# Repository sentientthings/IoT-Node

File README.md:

# IoT-Node
Hardware design files for the Sentient Things Iot Node

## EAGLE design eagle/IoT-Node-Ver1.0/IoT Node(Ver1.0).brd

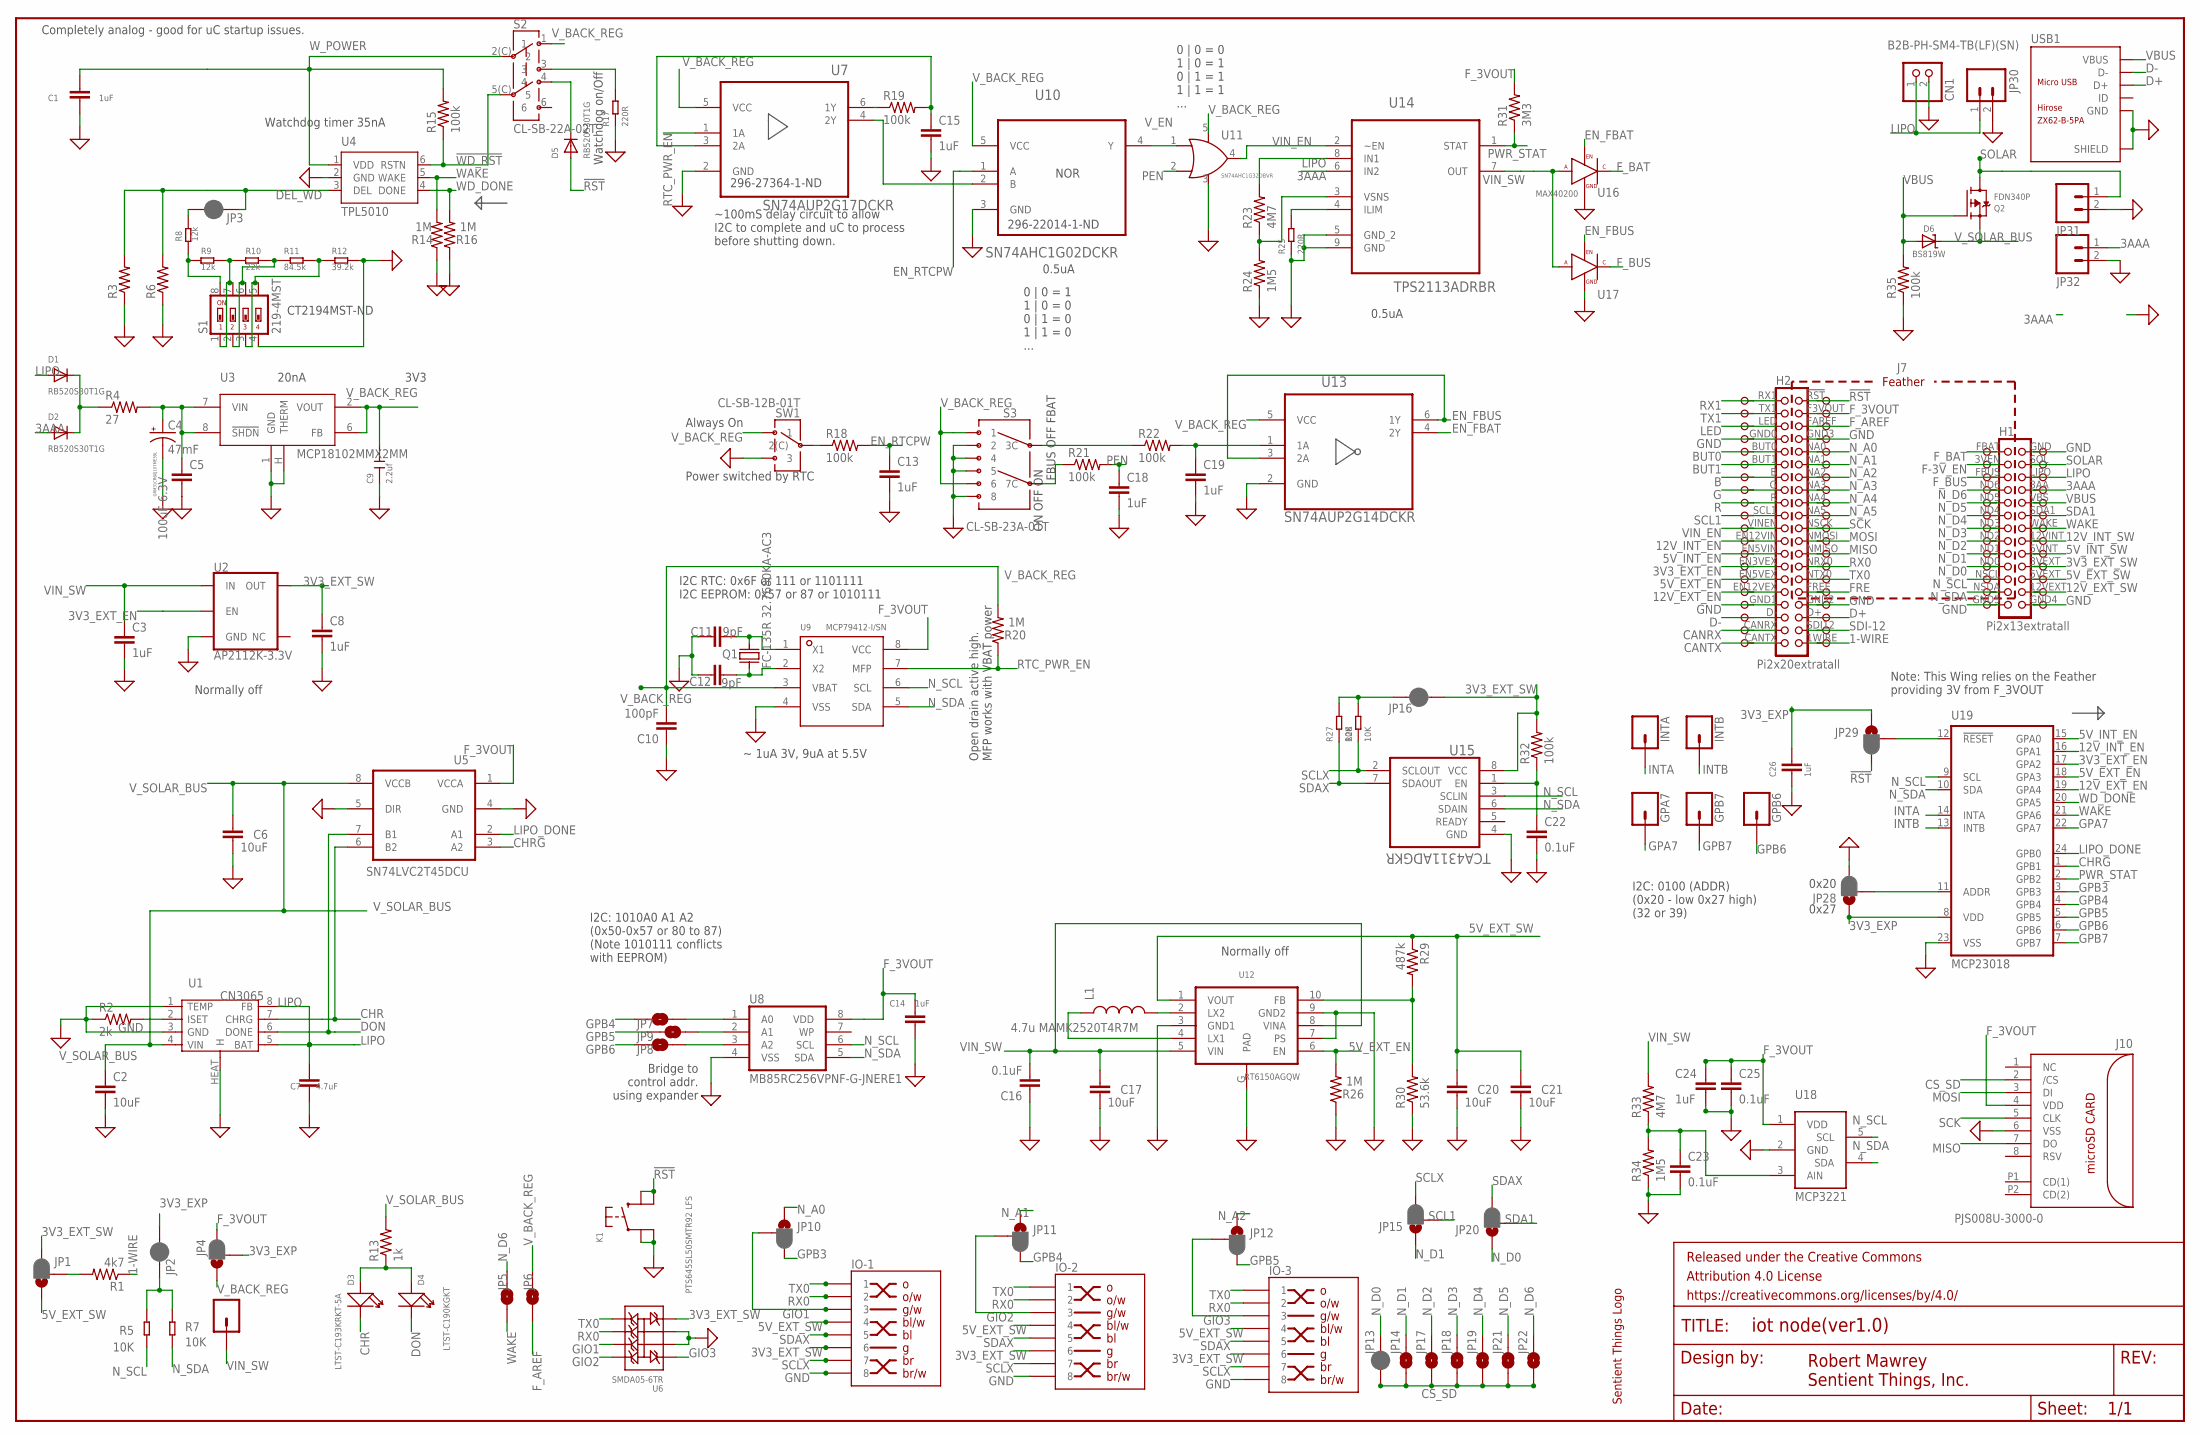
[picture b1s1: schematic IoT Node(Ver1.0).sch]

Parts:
C1, C3, C8, C13, C14, C15, C18, C19, C24, C26: 1uF; 0603-CAP; PARTNO CL10A105KP8NNNC
C2, C6, C17, C20, C21: 10uF; 0805; PARTNO CL21A106KPFNNNE
C4: 47mF; CAP-10.5MM; PARTNO FC0H473ZFTBR24
C5: 100uF 6.3V; C1206; PARTNO DNP
C7: 4.7uF; 0805; PARTNO CL10A475KP8NNNC
C9: 2.2uf; C0603; PARTNO CL10A106MQ8NNNC
C10: 100pF; 0805; PARTNO CL21C101JC61PNC
C11, C12: 9pF; 0603; PARTNO C1608C0G1H090D080AA
C16, C22, C23, C25: 0.1uF; 0603-CAP; PARTNO CL10F104ZB8NNNC
CN1: B2B-PH-SM4-TB(LF)(SN); JST-PH-2-SMT; PARTNO B2B-PH-SM4-TB(LF)(SN)?
D1, D2, D5: RB520S30T1G; SOD-523; PARTNO RB520S30T1G
D3: LTST-C193KRKT-5A; D0603; PARTNO LTST-C193KRKT-5A
D4: LTST-C190KGKT; D0603; PARTNO LTST-C190KGKT
D6: BS819W; SOD-123; PARTNO B5819WS-TP
FRAME1: FRAME-LEDGER; CREATIVE_COMMONS
GPA7: M01SMD-4.5X1.5; PAD-1.5X4.5; PARTNO DNP
GPB6, GPB7: M01SMD-4.5X1.5; PAD-1.5X4.5; PARTNO DNP
H1: Pi2x13extratall; 2X13PLACEMENT; PARTNO 2X13-ExtraTall
H2: Pi2x20extratall; 2X20PLACEMENT; PARTNO 2X20ExtraTall
INTA: M01SMD-4.5X1.5; PAD-1.5X4.5; PARTNO DNP
INTB: M01SMD-4.5X1.5; PAD-1.5X4.5; PARTNO DNP
IO-1, IO-2, IO-3: RJ45-8NODE-HOR; 73304111LF; PARTNO 73304-111LF
J1: CONN_01; 1X01; PARTNO DNP
J5, J6: M20IOTNODE; M20NODE; PARTNO DNP
J7: IOTNODEDOUBLE; IOTNODE; PARTNO DNP
J8, J9: M13NODE; 1X13NODE; PARTNO DNP
J10: PJS008U-3000-0; MICROSDYAMAICHI; PARTNO PJS008U-3000-0
JP1, JP4, JP10, JP11, JP12, JP15, JP20, JP28, JP29: JUMPER-SMT_3_1-NC_PASTE_NO-SILK; SMT-JUMPER_3_1-NC_PASTE_NO-SILK; PARTNO DNP
JP2, JP3, JP13, JP16: JUMPER-SMT_2_NC_PASTE_NO-SILK; SMT-JUMPER_2_NC_PASTE_NO-SILK; PARTNO DNP
JP5, JP6, JP7, JP8, JP9, JP14, JP17, JP18, JP19, JP21, JP22: JUMPER-SMT_2_NO_NO-SILK; SMT-JUMPER_2_NO_NO-SILK; PARTNO DNP
JP30: M021X02_LOCK_FEM; 1X02_LOCK_FEM; PARTNO 691322110002
JP31: M02SOCK; 1X02-3.5-HOR; PARTNO DNP
JP32: M02PLUG; 1X02_3.5TERM; PARTNO 691321100002
K1: PTS645SL50SMTR92 LFS; TACTILE6MM-ESWITCH; PARTNO PTS645SL50SMTR92 LFS
L1: 4.7u MAMK2520T4R7M; 2520; PARTNO MAMK2520T2R2M
N1: SENTIENTLOGO-ULP; SENTIENT_THINGS+50MM_TPLACE_BMP; PARTNO DNP
Q1: FC-135R 32.7680KA-AC3; FC135; PARTNO FC-135R 32.7680KA-AC3
Q2: FDN340P; SOT23-R; PARTNO FDN340P
R1: 4k7; 0603-RES; PARTNO RC0603JR-074K7L
R2: 2k; R0603; PARTNO ERJ-3GEYJ202V
R3, R6: RESISTOR0603-RES; 0603-RES; PARTNO DNP
R4: 27; 0603-RES; PARTNO RC0603JR-0727RL
R5, R7, R27, R28: 10K; R0603; PARTNO ERJ-3GEYJ103V
R8, R9: 12k; R0603; PARTNO ERJ-3GEYJ123V
R10: 22k; R0603; PARTNO ERJ-3GEYJ223V
R11: 84.5k; 0603; PARTNO RC0603FR-0784K5L
R12: 39.2k; 0603; PARTNO RC0603FR-0739K2L
R13: 1k; R0603; PARTNO ERJ-3GEYJ102V
R14, R16, R20, R26: 1M; 0603; PARTNO ERJ-3GEYJ105V
R15, R18, R19, R21, R22, R32, R35: 100k; 0603-RES; PARTNO ERJ-3GEYJ104V
R17, R25: 220R; R0603; PARTNO ERJ-3GEYJ221V
R23, R33: 4M7; 0603-RES; PARTNO ERJ-3GEYJ475V
R24, R34: 1M5; 0603-RES; PARTNO ERJ-3GEYJ155V
R29: 487k; 0603-RES; PARTNO RC0603FR-07487KL
R30: 53.6k; 0603-RES; PARTNO RC0603FR-0753K6L
R31: 3M3; 0603-RES; PARTNO ERJ-3GEYJ335V
S1: 219-4MST; SMS-004; PARTNO 219-4MST
S2: CL-SB-22A-02T; CL-SB-22A; PARTNO CL-SB-22A-02T
S3: CL-SB-23A-01T; CL-SB-23A; PARTNO CL-SB-23A-01T
SW1: CL-SB-12B-01T; CL-SB-12B; PARTNO CL-SB-12B-01T
U1: CN3065; DFN8; PARTNO CN3065
U2: AP2112K-3.3V; SOT23-5; PARTNO AP2112K-3.3TRG
U3: MCP18102MMX2MM; 8VDFN; PARTNO MCP1810T-33I/J8A
U4: TPL5010; SOT23-6; PARTNO TPL5010DDCT
U5: SN74LVC2T45DCU; US8-DCU; PARTNO SN74LVC2T45DCUR
U6: SMDA05-6TR; SOIC-8-STANDARD; PARTNO SMDA05-6TR
U7: SN74AUP2G17DCKR; SOT65P210X110-6N
U8: MB85RC256VPNF-G-JNERE1; SO08; PARTNO MB85RC256VPNF-G-JNERE1
U9: MCP79412-I/SN; RTC_MCP7941X; PARTNO MCP79412-I/SN
U10: SN74AHC1G02DCKR; SOT65P210X110-5N
U11: SN74AHC1G32DBVR; SOT23-5; PARTNO SN74AHC1G32DBVR
U12: RT6150AGQW; DFN103X3; PARTNO RT6150AGQW
U13: SN74AUP2G14DCKR; SOT65P210X110-6N
U14: TPS2113ADRBR; SON65P300X300X100-9N
U15: TCA4311ADGKR; SOP65P490X110-8N; PARTNO TCA4311ADGKR
U16, U17: MAX40200; SOT23-5; PARTNO MAX40200AUK+T
U18: MCP3221; SOT23-5; PARTNO MCP3221A5T-E/OT
U19: MCP23018; QFN24-4MM; PARTNO MCP23018-E/MJ
USB1: ZX62-B-5PA; MICRO-USB5+6P-SMD-0.65-AB; PARTNO ZX62-B-5PA(33)

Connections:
1-WIRE: J6.20, J7.1WIRE (40), R1.1
3AAA: D2.A, J7.3AA (60), J9.4, JP32.1, U14.6 (IN2)
3V3_EXP: C26.1, JP2.1, JP4.2, JP28.1, JP29.1, U19.8 (VDD)
3V3_EXT_EN: J5.14, J7.EN3VEX (27), U2.3 (EN), U19.17 (GPA2)
3V3_EXT_SW: C8.1, IO-1.6, IO-2.6, IO-3.6, J7.3VEXT (48), J9.10, JP1.3, JP16.1, R32.2, U2.5 (OUT), U6.8, U15.8 (VCC)
5V_EXT_EN: J5.15, J7.EN5VEX (29), R26.2, U12.6 (EN), U19.18 (GPA3)
5V_EXT_SW: C20.1, C21.1, IO-1.4, IO-2.4, IO-3.4, J7.5VEXT (46), J9.11, JP1.1, R29.1, U12.1 (VOUT)
5V_INT_EN: J5.13, J7.EN5VIN (25), U19.15 (GPA0)
5V_INT_SW: J7.5VINT (50), J9.9
12V_EXT_EN: J5.16, J7.EN12VEX (31), U19.19 (GPA4)
12V_EXT_SW: J7.12VEXT (44), J9.12
12V_INT_EN: J5.12, J7.EN12VIN (23), U19.16 (GPA1)
12V_INT_SW: J7.12VINT (52), J9.8
!RESET: JP29.2, U19.12 (!RESET)
!RST: D5.A, J6.1, J7.!RST (2), JP29.3, K1.2 (B0), K1.3 (B1)
!WD_RST: R15.1, S2.5(C) (5), U4.6 (RSTN)
B: J5.7, J7.B (13)
BUT0: J5.5, J7.BUT0 (9)
BUT1: J5.6, J7.BUT1 (11)
CANRX: J5.19, J7.CANRX (37)
CANTX: J5.20, J7.CANTX (39)
CHR: D3.-, U1.7 (CHRG), U5.6 (B2)
CHRG: U5.3 (A2), U19.1 (GPB1)
CS_SD: J10.2 (/CS), JP13.1, JP14.1, JP17.1, JP18.1, JP19.1, JP21.1, JP22.1
D+: J6.18, J7.D+ (36), USB1.3 (D+)
D-: J5.18, J7.D- (35), USB1.2 (D-)
DEL_WD: JP3.1, R3.2, R6.2, U4.3 (DEL)
DON: D4.-, U1.6 (DONE), U5.7 (B1)
EN_FBAT: U13.4 (2Y), U16.3 (EN)
EN_FBUS: U13.3 (2A), U13.6 (1Y), U17.3 (EN)
EN_RTCPW: C13.1, R18.2, U10.1 (A)
F-3V_EN: J7.3VEN (63), J8.2
FA0: JP7.2, U8.1 (A0)
FA1: JP9.2, U8.2 (A1)
FA2: JP8.2, U8.3 (A2)
FRE: J6.16, J7.FREE (32)
F_3VOUT: C14.1, C24.1, C25.1, J6.2, J7.F3VOUT (4), J10.4 (VDD), JP4.3, R31.2, U5.1 (VCCA), U8.8 (VDD), U9.8 (VCC), U18.1 (VDD)
F_AREF: J6.3, J7.FAREF (6), JP6.2
F_BAT: J7.FBAT (65), J8.1, U16.5 (C)
F_BUS: J7.FBUS (61), J8.3, U17.5 (C)
G: J5.8, J7.G (15)
GIO1: IO-1.3, JP10.2, U6.3
GIO2: IO-2.3, JP11.2, U6.4
GIO3: IO-3.3, JP12.2, U6.5
GND: C1.2, C2.2, C3.2, C4.-VE (-), C5.2, C6.2, C7.2, C8.2, C9.1, C10.1, C11.1 (ANODE), C12.1 (ANODE), C13.2, C14.2, C15.2, C16.1, C17.2, C18.2, C19.2, C20.2, C21.2, C22.2, C23.2, C24.2, C25.2, C26.2, CN1.2 (1), IO-1.8, IO-2.8, IO-3.8, J5.4, J5.17, J6.4, J6.17, J7.GND (66), J7.GND0 (7), J7.GND1 (33), J7.GND2 (34), J7.GND3 (8), J7.GND4 (42), J7.GND5 (41), J8.13, J9.1, J9.13, J10.6 (VSS), JP28.3, JP30.2, JP31.2, JP32.2, K1.1 (A0), K1.4 (A1), R2.1, R3.1, R6.1, R12.2, R14.1, R16.1, R17.1, R24.1, R25.1, R26.1, R30.1, R34.1, R35.1, S1.4, S3.2, S3.4, S3.5, S3.8, SW1.3, U1.1 (TEMP), U1.3 (GND), U1.HEAT (H), U2.2 (GND), U3.1 (GND), U3.H (THERM), U4.2 (GND), U5.4 (GND), U5.5 (DIR), U6.6, U6.7, U7.2 (GND), U8.4 (VSS), U9.4 (VSS), U10.3 (GND), U11.3 (G), U12.3 (GND1), U12.7 (PS), U12.9 (GND2), U12.G (PAD), U13.2 (GND), U14.5 (GND_2), U14.9 (GND), U15.4 (GND), U16.2 (G), U17.2 (G), U18.2 (GND), U19.23 (VSS), USB1.5 (GND), USB1.P1 (SHIELD), USB1.P2 (SHIELD), USB1.P3 (SHIELD), USB1.P4 (SHIELD), USB1.P5 (SHIELD), USB1.P6 (SHIELD)
GPA7: GPA7.P$1, U19.22 (GPA7)
GPB3: JP10.3, U19.3 (GPB3)
GPB4: JP7.1, JP11.3, U19.4 (GPB4)
GPB5: JP9.1, JP12.3, U19.5 (GPB5)
GPB6: GPB6.P$1, JP8.1, U19.6 (GPB6)
GPB7: GPB7.P$1, U19.7 (GPB7)
I2CPWR: JP2.2, R5.2, R7.2
INTA: INTA.P$1, U19.14 (INTA)
INTB: INTB.P$1, U19.13 (INTB)
LED: J5.3, J7.LED (5)
LIPO: C7.1, CN1.1 (2), D1.A, J7.LIPO (62), J9.3, JP30.1, R23.2, U1.5 (BAT), U1.8 (FB), U14.8 (IN1)
LIPO_DONE: U5.2 (A1), U19.24 (GPB0)
MISO: J6.13, J7.NMISO (26), J10.7 (DO)
MOSI: J6.12, J7.NMOSI (24), J10.3 (DI)
unnamed: JP3.2, R8.2
unnamed: R2.2, U1.2 (ISET)
unnamed: R17.2, S2.3
unnamed: R19.1, U7.6 (1Y)
unnamed: D3.+, D4.+, R13.1
unnamed: R18.1, SW1.C(2) (2(C))
unnamed: R25.2, U14.4 (ILIM)
unnamed: JP28.2, U19.11 (ADDR)
unnamed: R23.1, R24.2, U14.3 (VSNS)
unnamed: D1.K (C), D2.K (C), R4.1
unnamed: D5.K (C), S2.4
unnamed: C15.1, R19.2, U7.3 (2A)
unnamed: C11.2 (CATHODE), Q1.X2 (2), U9.1 (X1)
unnamed: C12.2 (CATHODE), Q1.X1 (1), U9.2 (X2)
unnamed: JP1.2, R1.2
unnamed: U7.4 (2Y), U10.2 (B)
unnamed: R9.2, R10.1, S1.1, S1.7
unnamed: R10.2, R11.1, S1.2, S1.6
unnamed: R11.2, R12.1, S1.3, S1.5
unnamed: R8.1, R9.1, S1.8
unnamed: C23.1, R33.1, R34.2, U18.3 (AIN)
unnamed: JP16.2, R27.2, R28.2
unnamed: L1.L2 (2), U12.2 (LX2)
unnamed: L1.L1 (1), U12.4 (LX1)
unnamed: R29.2, R30.2, U12.10 (FB)
unnamed: R21.1, S3.7(C) (7C)
unnamed: C22.1, R32.1, U15.1 (EN)
unnamed: C19.1, R22.2, U13.1 (1A)
unnamed: R22.1, S3.3(C) (3C)
N_A0: J6.5, J7.NA0 (10), JP10.1
N_A1: J6.6, J7.NA1 (12), JP11.1
N_A2: J6.7, J7.NA2 (14), JP12.1
N_A3: J6.8, J7.NA3 (16)
N_A4: J6.9, J7.NA4 (18)
N_A5: J6.10, J7.NA5 (20)
N_D0: J7.ND0 (47), J8.10, JP13.2, JP20.1
N_D1: J7.ND1 (49), J8.9, JP14.2, JP15.1
N_D2: J7.ND2 (51), J8.8, JP17.2
N_D3: J7.ND3 (53), J8.7, JP18.2
N_D4: J7.ND4 (55), J8.6, JP19.2
N_D5: J7.ND5 (57), J8.5, JP21.2
N_D6: J7.ND6 (59), J8.4, JP5.1, JP22.2
N_SCL: J7.NSCL (45), J8.11, R5.1, U8.6 (SCL), U9.6 (SCL), U15.3 (SCLIN), U18.5 (SCL), U19.9 (SCL)
N_SDA: J7.NSDA (43), J8.12, R7.1, U8.5 (SDA), U9.5 (SDA), U15.6 (SDAIN), U18.4 (SDA), U19.10 (SDA)
PEN: C18.1, R21.2, U11.2 (B)
PWR_STAT: R31.1, U14.1 (STAT), U19.2 (GPB2)
R: J5.9, J7.R (17)
RTC_PWR_EN: R20.1, U7.1 (1A), U9.7 (MFP)
RX0: IO-1.2, IO-2.2, IO-3.2, J6.14, J7.NRX0 (28), U6.2
RX1: J5.1, J7.RX1 (1)
SCK: J6.11, J7.NSCK (22), J10.5 (CLK)
SCL1: J5.10, J7.SCL1 (19), JP15.2
SCLX: IO-1.7, IO-2.7, IO-3.7, JP15.3, R28.1, U15.2 (SCLOUT)
SDA1: J7.SDA1 (56), J9.6, JP20.2
SDAX: IO-1.5, IO-2.5, IO-3.5, JP20.3, R27.1, U15.7 (SDAOUT)
SDI-12: J6.19, J7.SDI12 (38)
SOLAR: J7.SOL (64), J9.2, JP31.1, Q2.3 (D)
TX0: IO-1.1, IO-2.1, IO-3.1, J6.15, J7.NTX0 (30), U6.1
TX1: J5.2, J7.TX1 (3)
VBUS: D6.A, J7.VBS (58), J9.5, Q2.1 (G), R35.2, USB1.1 (VBUS)
VIN_EN: J5.11, J7.VINEN (21), U11.4 (Y), U14.2 (~EN)
VIN_SW: C3.1, C16.2, C17.1, J1.1, R33.2, U2.1 (IN), U12.5 (VIN), U12.8 (VINA), U14.7 (OUT), U16.1 (A), U17.1 (A)
V_BACK: C4.+VE (+), C5.1, R4.2, U3.7 (VIN), U3.8 (!SHDN)
V_BACK_REG: C9.2, C10.2, JP4.1, JP6.1, R20.2, S2.1, S3.1, S3.6, SW1.1, U3.2 (VOUT), U3.6 (FB), U7.5 (VCC), U9.3 (VBAT), U10.5 (VCC), U11.5 (V), U13.5 (VCC)
V_EN: U10.4 (Y), U11.1 (A)
V_SOLAR_BUS: C2.1, C6.1, D6.C, Q2.2 (S), R13.2, U1.4 (VIN), U5.8 (VCCB)
WAKE: J7.WAKE (54), J9.7, JP5.2, R14.2, U4.5 (WAKE), U19.21 (GPA6)
WD_DONE: R16.2, U4.4 (DONE), U19.20 (GPA5)
W_POWER: C1.1, R15.2, S2.2(C) (2), U4.1 (VDD)

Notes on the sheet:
Open drain active high. MFP works with VBAT power
Watchdog timer 35nA
~ 1uA 3V, 9uA at 5.5V
Always On Power switched by RTC
GRM31CR60J107ME39L
20nA
0.5uA
3V3
Watchdog on/Off
I2C RTC: 0x6F or 111 or 1101111 I2C EEPROM: 0x57 or 87 or 1010111
I2C: 0100 (ADDR) (0x20 - low 0x27 high) (32 or 39)
NOR
Normally off
0 | 0 = 1 1 | 0 = 0 0 | 1 = 0 1 | 1 = 0 ...
I2C: 1010A0 A1 A2 (0x50-0x57 or 80 to 87) (Note 1010111 conflicts with EEPROM)
Note: This Wing relies on the Feather providing 3V from F_3VOUT
0x20
0x27
Bridge to control addr. using expander
Robert Mawrey Sentient Things, Inc.
Completely analog - good for uC startup issues.
~100mS delay circuit to allow I2C to complete and uC to process before shutting down.
296-27364-1-ND
296-22014-1-ND
CT2194MST-ND
ON OFF ON
FBUS OFF FBAT
0 | 0 = 0 1 | 0 = 1 0 | 1 = 1 1 | 1 = 1 ...

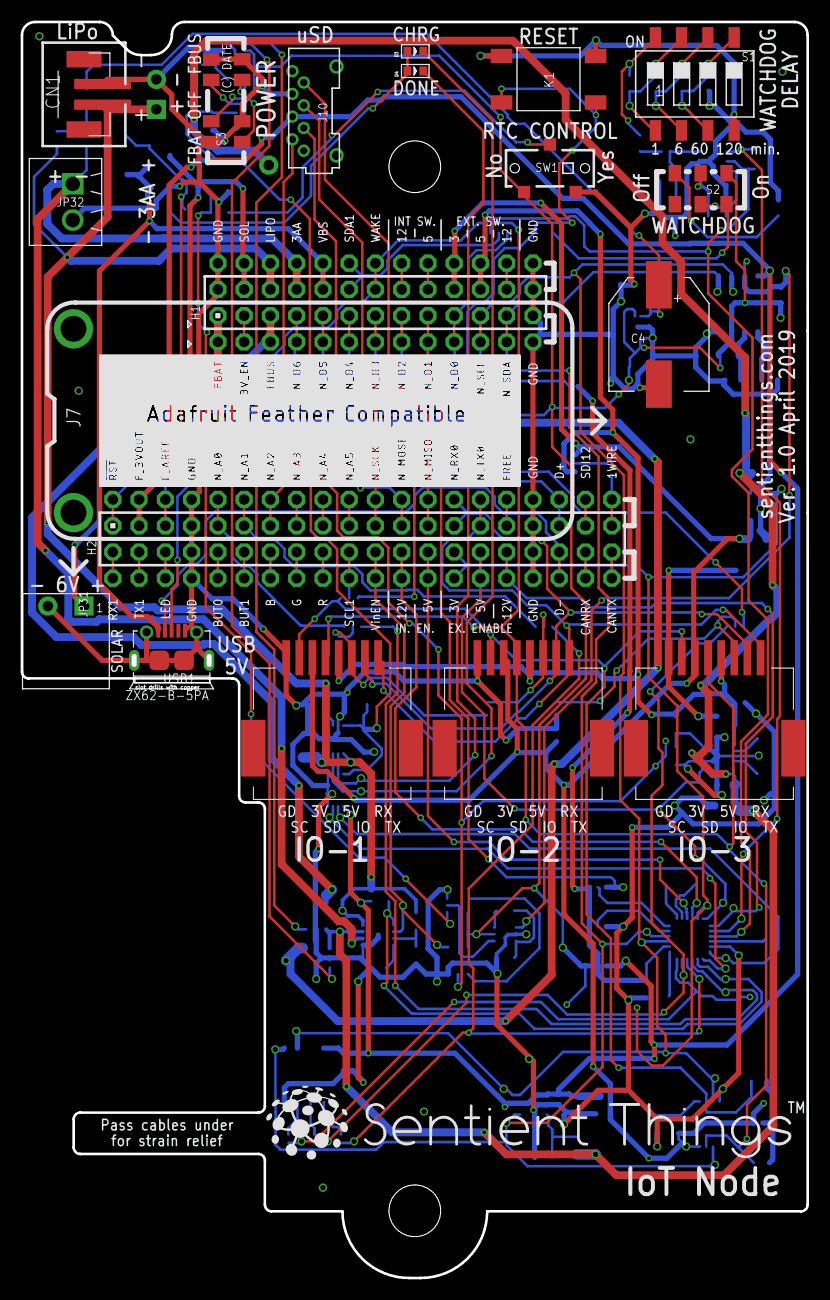
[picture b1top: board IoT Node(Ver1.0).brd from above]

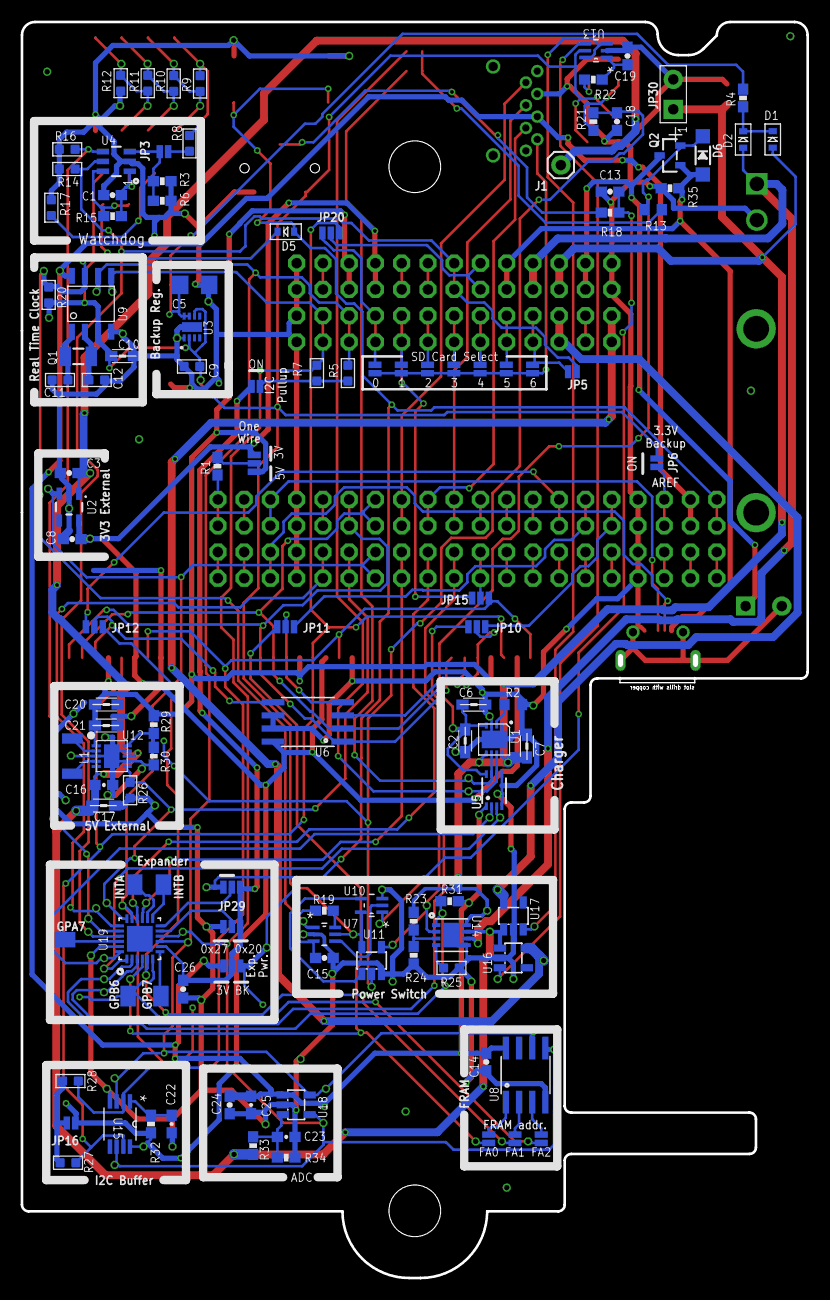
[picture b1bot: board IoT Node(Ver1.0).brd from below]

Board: 2 copper layers, 76.0 x 121.5 mm, 142 parts (117 on the bottom side), 128 nets.

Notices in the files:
parts and their libraries:
microbuilder: This work is placed in the public domain, and may be freely used for commercial and non-commercial work with the following conditions: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
SparkFun-IC-Power: Licensing: Creative Commons ShareAlike 4.0 International - https://creativecommons.org/licenses/by-sa/4.0
